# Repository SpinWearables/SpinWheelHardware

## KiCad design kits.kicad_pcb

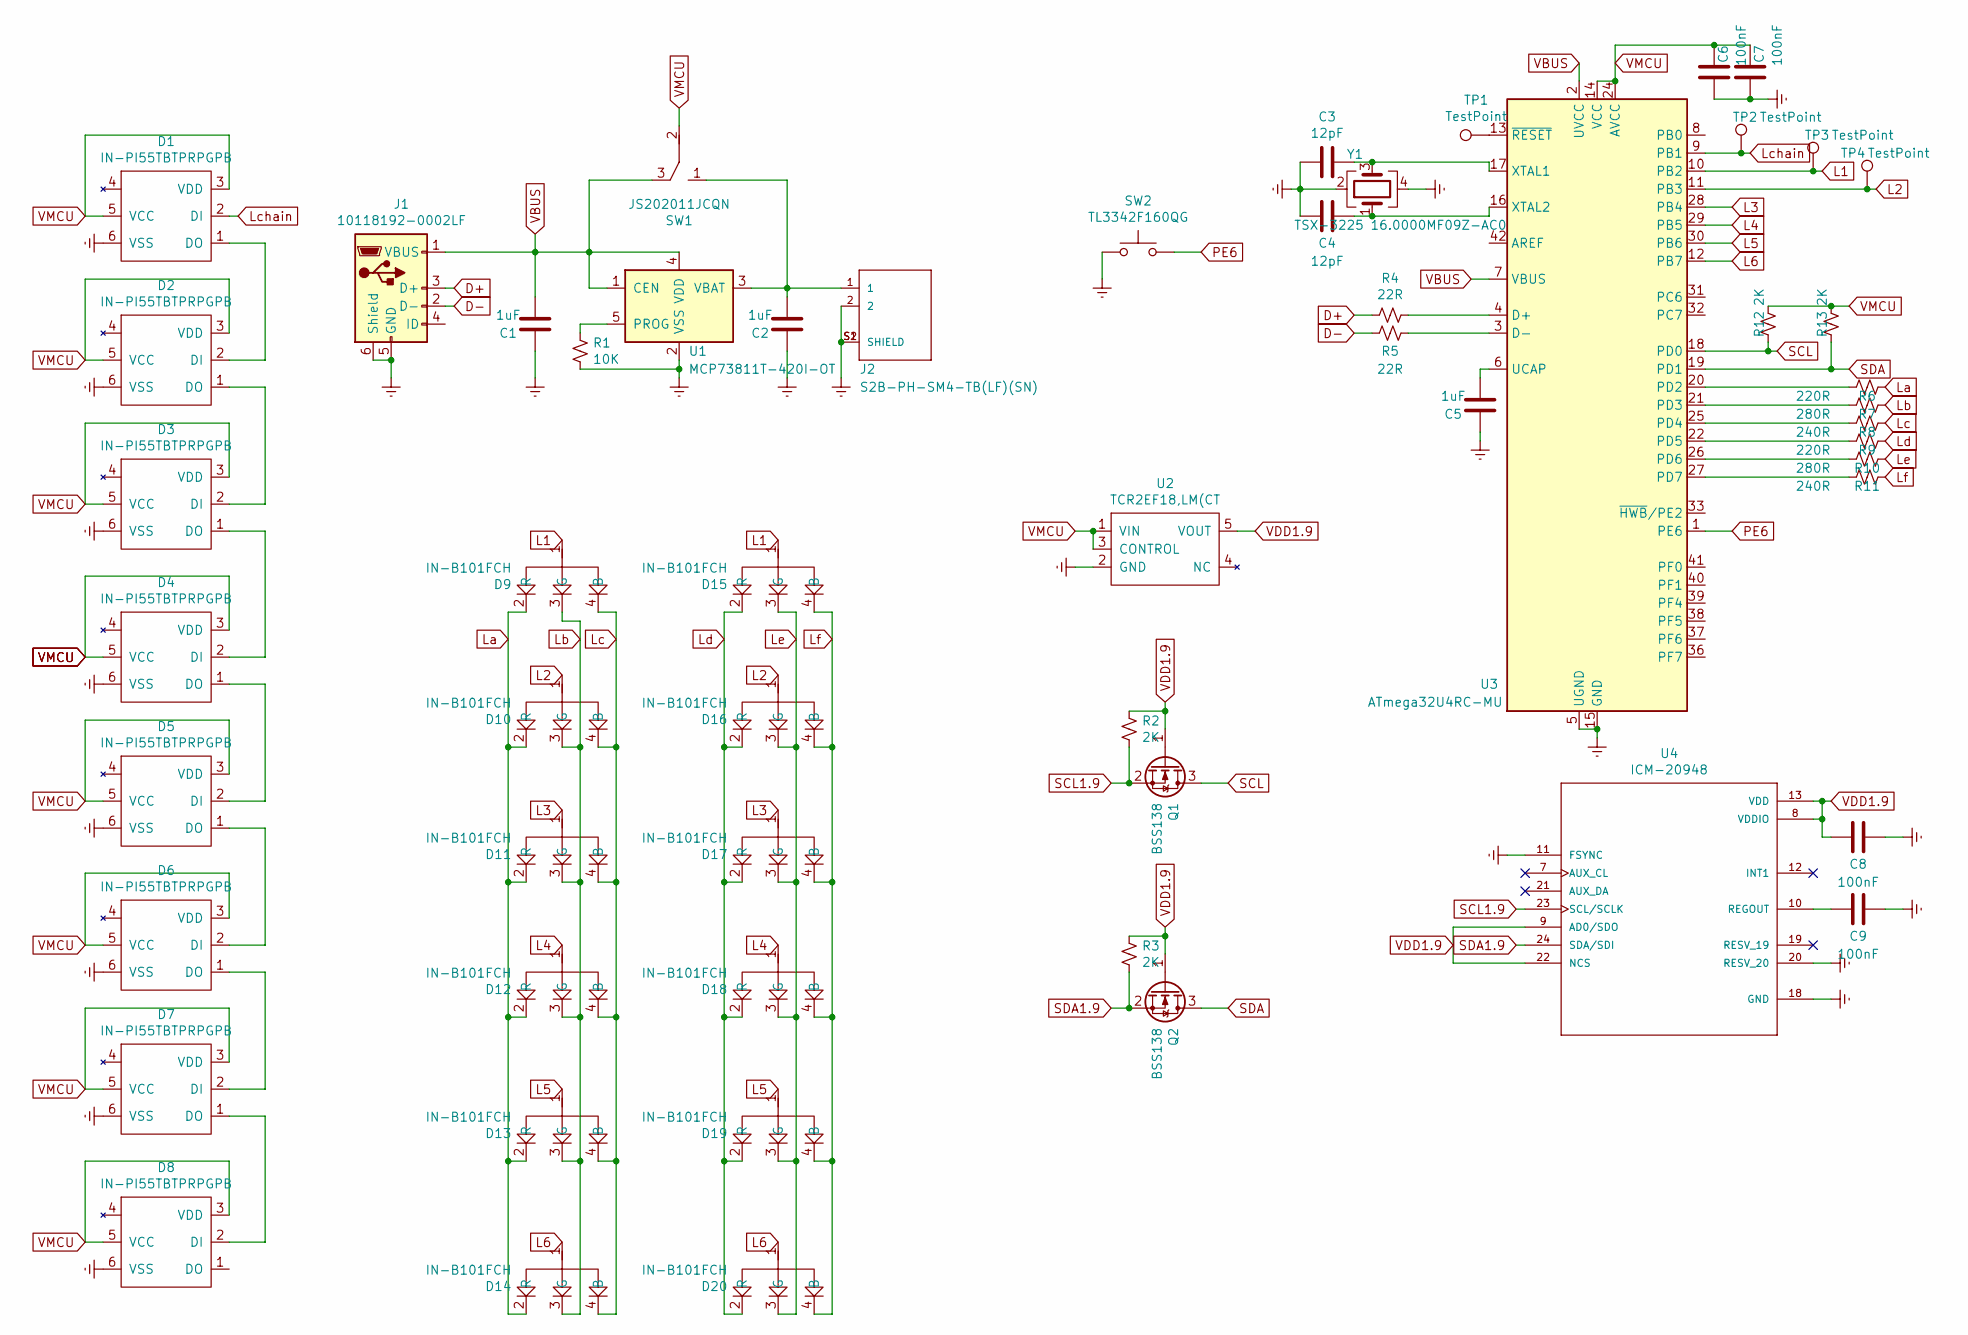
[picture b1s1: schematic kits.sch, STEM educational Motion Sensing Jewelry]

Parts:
C1, C2, C5: 1uF; C_0603_1608Metric
C3, C4: 12pF; C_0603_1608Metric
C6, C7, C8, C9: 100nF; C_0603_1608Metric
D1, D2, D3, D4, D5, D6, D7, D8: IN-PI55TBTPRPGPB
D9, D10, D11, D12, D13, D14, D15, D16, D17, D18, D19, D20: IN-B101FCH
J1: 10118192-0002LF
J2: S2B-PH-SM4-TB(LF)(SN); JST_S2B-PH-SM4-TB(LF)(SN)
Q1, Q2: BSS138; SOT-23
R1: 10K; R_0603_1608Metric
R2, R3, R12, R13: 2K; R_0603_1608Metric
R4, R5: 22R; R_0603_1608Metric
R6, R9: 220R; R_0603_1608Metric
R7, R10: 280R; R_0603_1608Metric
R8, R11: 240R; R_0603_1608Metric
SW1: JS202011JCQN
SW2: TL3342F160QG; SW_SPST_TL3342
TP1, TP2, TP3, TP4: TestPoint; TestPoint_Pad_D1.0mm
U1: MCP73811T-420I-OT; SOT-23-5
U2: TCR2EF18,LM(CT; SOT-23-5
U3: ATmega32U4RC-MU; QFN-44-1EP_7x7mm_P0.5mm_EP5.2x5.2mm
U4: ICM-20948; QFN40P300X300X105-25N
Y1: TSX-3225 16.0000MF09Z-AC0; Crystal_SMD_SeikoEpson_FA238-4Pin_3.2x2.5mm

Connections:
D+: J1.3 (D+), R4.2
D-: J1.2 (D-), R5.2
Earth: C1.1, C2.1, C3.2, C4.2, C5.1, C6.2, C7.2, C8.1, C9.1, D1.6 (VSS), D2.6 (VSS), D3.6 (VSS), D4.6 (VSS), D5.6 (VSS), D6.6 (VSS), D7.6 (VSS), D8.6 (VSS), J1.5 (GND), J1.6 (Shield), J2.2, J2.S1 (SHIELD), J2.S2 (SHIELD), R1.2, SW2.1, U1.2 (VSS), U2.2 (GND), U3.5 (UGND), U3.15 (GND), U3.23 (GND), U3.35 (GND), U3.43 (GND), U3.45 (GND), U4.11 (FSYNC), U4.18 (GND), U4.20 (RESV_20), Y1.2, Y1.4
L1: D9.1, D15.1, TP3.1, U3.10 (PB2)
L2: D10.1, D16.1, TP4.1, U3.11 (PB3)
L3: D11.1, D17.1, U3.28 (PB4)
L4: D12.1, D18.1, U3.29 (PB5)
L5: D13.1, D19.1, U3.30 (PB6)
L6: D14.1, D20.1, U3.12 (PB7)
La: D9.2 (R), D10.2 (R), D11.2 (R), D12.2 (R), D13.2 (R), D14.2 (R), R6.1
Lb: D9.3 (G), D10.3 (G), D11.3 (G), D12.3 (G), D13.3 (G), D14.3 (G), R7.1
Lc: D9.4 (B), D10.4 (B), D11.4 (B), D12.4 (B), D13.4 (B), D14.4 (B), R8.1
Lchain: D1.2 (DI), TP2.1, U3.9 (PB1)
Ld: D15.2 (R), D16.2 (R), D17.2 (R), D18.2 (R), D19.2 (R), D20.2 (R), R9.1
Le: D15.3 (G), D16.3 (G), D17.3 (G), D18.3 (G), D19.3 (G), D20.3 (G), R10.1
Lf: D15.4 (B), D16.4 (B), D17.4 (B), D18.4 (B), D19.4 (B), D20.4 (B), R11.1
unnamed: C2.2, J2.1, SW1.1, U1.3 (VBAT)
unnamed: C3.1, U3.17 (XTAL1), Y1.3
unnamed: C4.1, U3.16 (XTAL2), Y1.1
unnamed: C5.2, U3.6 (UCAP)
unnamed: C9.2, U4.10 (REGOUT)
unnamed: D1.1 (DO), D2.2 (DI)
unnamed: D2.1 (DO), D3.2 (DI)
unnamed: D3.1 (DO), D4.2 (DI)
unnamed: D4.1 (DO), D5.2 (DI)
unnamed: D5.1 (DO), D6.2 (DI)
unnamed: D6.1 (DO), D7.2 (DI)
unnamed: D7.1 (DO), D8.2 (DI)
unnamed: R1.1, U1.5 (PROG)
unnamed: R4.1, U3.4 (D+)
unnamed: R5.1, U3.3 (D-)
unnamed: R6.2, U3.20 (PD2)
unnamed: R7.2, U3.21 (PD3)
unnamed: R8.2, U3.25 (PD4)
unnamed: R9.2, U3.22 (PD5)
unnamed: R10.2, U3.26 (PD6)
unnamed: R11.2, U3.27 (PD7)
unnamed: TP1.1, U3.13 (~RESET)
PE6: SW2.2, U3.1 (PE6)
SCL: Q1.3 (D), R12.1, U3.18 (PD0)
SCL1.9: Q1.2 (S), R2.2, U4.23 (SCL/SCLK)
SDA: Q2.3 (D), R13.1, U3.19 (PD1)
SDA1.9: Q2.2 (S), R3.2, U4.24 (SDA/SDI)
VBUS: C1.2, J1.1 (VBUS), SW1.3, U1.1 (CEN), U1.4 (VDD), U3.2 (UVCC), U3.7 (VBUS)
VDD1.9: C8.2, Q1.1 (G), Q2.1 (G), R2.1, R3.1, U2.5 (VOUT), U4.8 (VDDIO), U4.9 (AD0/SDO), U4.13 (VDD), U4.22 (NCS)
VMCU: C6.1, C7.1, D1.3 (VDD), D1.5 (VCC), D2.3 (VDD), D2.5 (VCC), D3.3 (VDD), D3.5 (VCC), D4.3 (VDD), D4.5 (VCC), D5.3 (VDD), D5.5 (VCC), D6.3 (VDD), D6.5 (VCC), D7.3 (VDD), D7.5 (VCC), D8.3 (VDD), D8.5 (VCC), R12.2, R13.2, SW1.2, U2.1 (VIN), U2.3 (CONTROL), U3.14 (VCC), U3.24 (AVCC), U3.34 (VCC), U3.44 (AVCC)

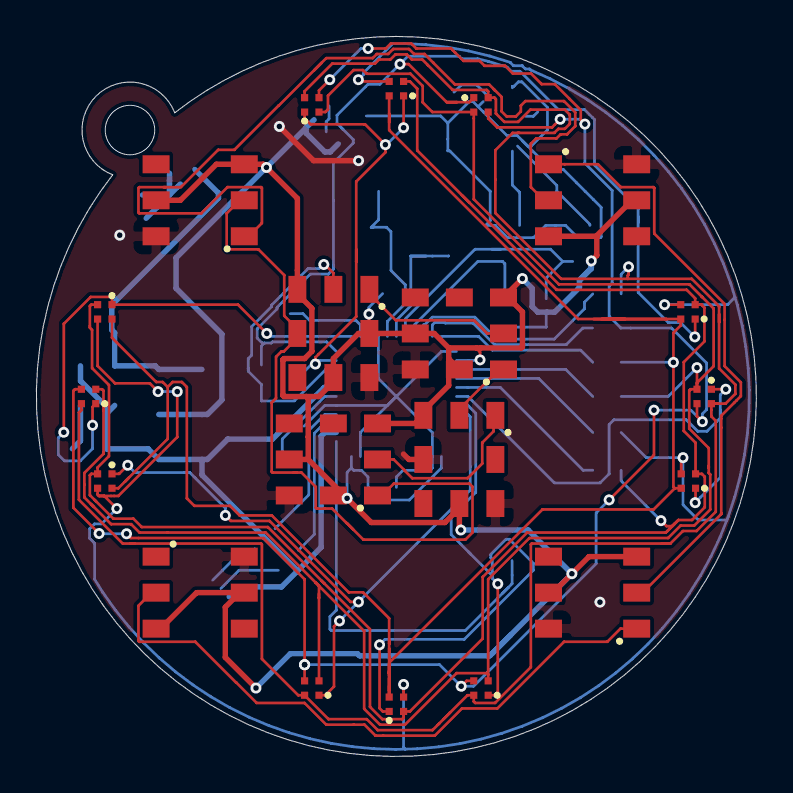
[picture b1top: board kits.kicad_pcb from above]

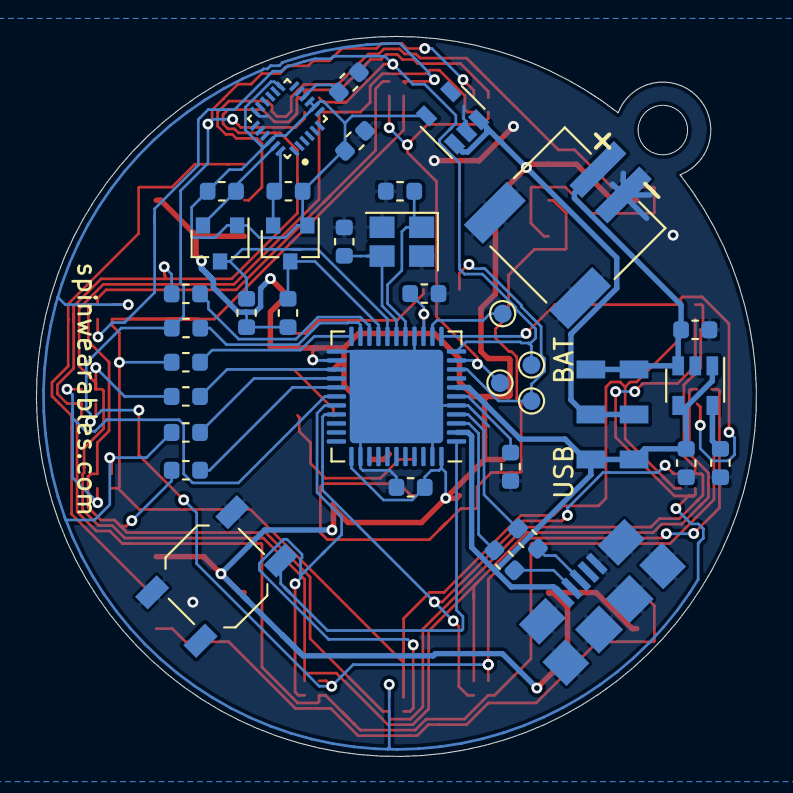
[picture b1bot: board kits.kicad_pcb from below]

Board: 2 copper layers, 40.0 x 40.0 mm, 57 parts (37 on the bottom side), 46 nets.

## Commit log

2020-02-17 Add all design files.
2020-02-17 Cleanup of python timelapse scripts.
2020-02-17 Move a cap that obstructs the battery jack.
2020-05-06 Update kicad version.
